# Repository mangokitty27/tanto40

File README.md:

# tanto40
A 40% keeb inspired by the Katana60

uses redragon low profile switches and arduino promicro

created in kicad

.dxf file show geometry of layout

qmk layout.hex made with https://kbfirmware.com/

redragon switch footprint from github.com/rgoulter

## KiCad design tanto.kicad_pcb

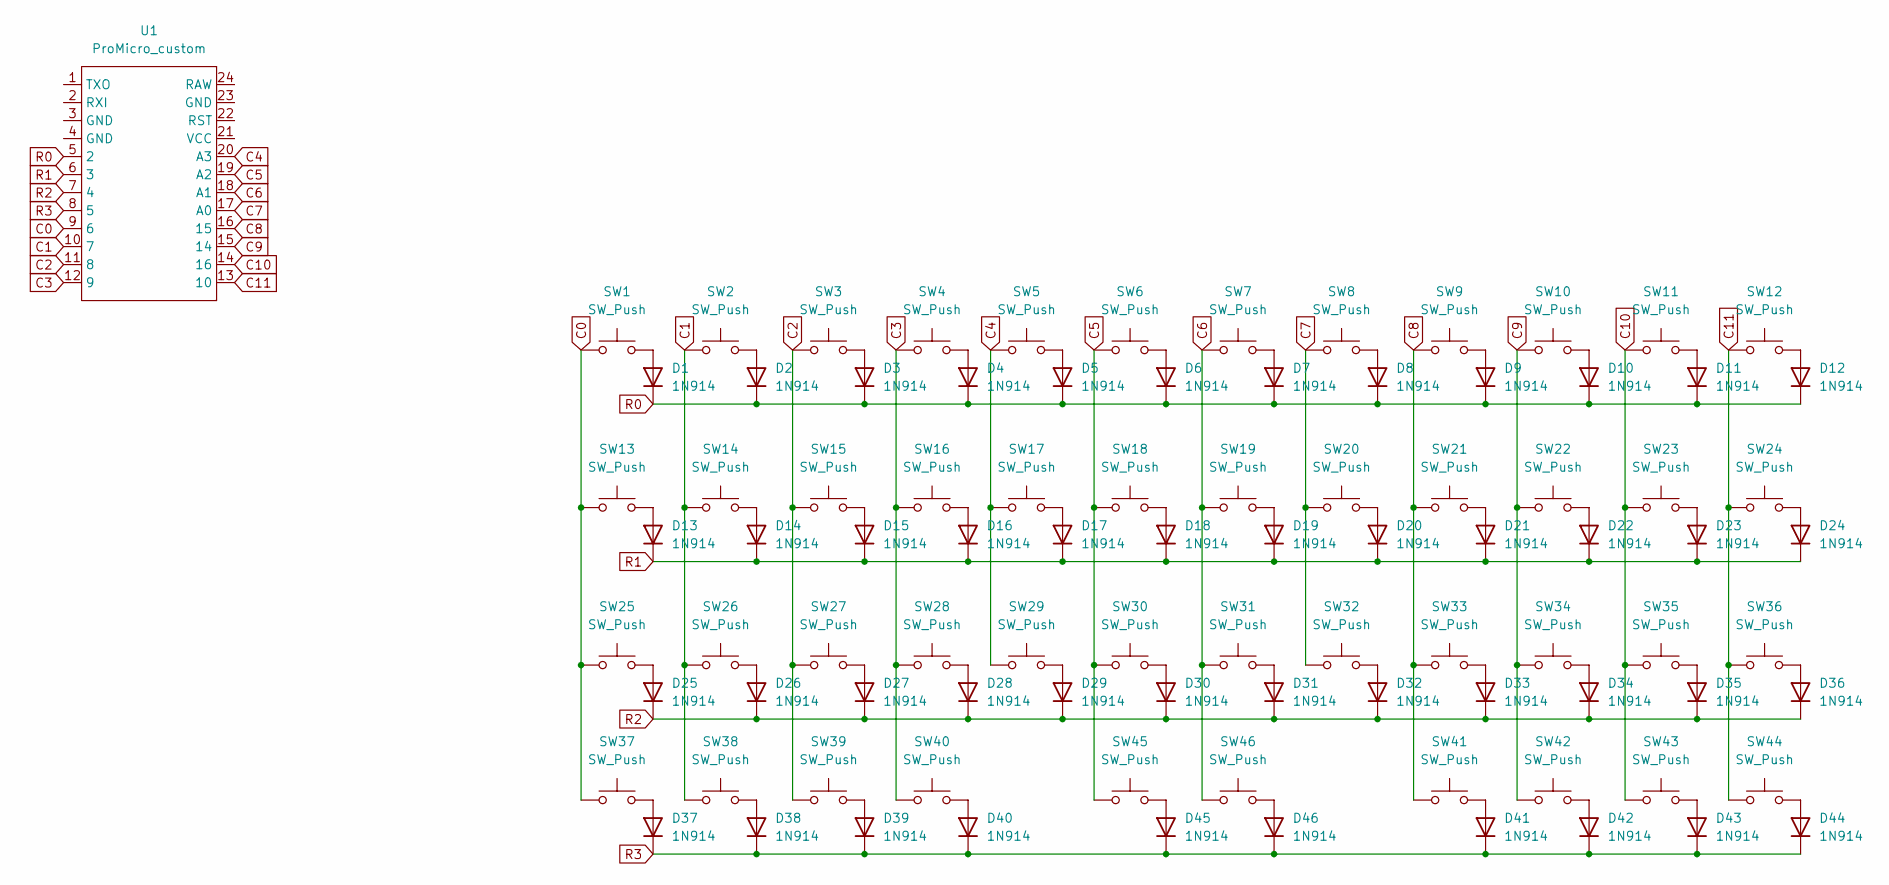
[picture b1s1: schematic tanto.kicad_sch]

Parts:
D1, D2, D3, D4, D5, D6, D7, D8, D9, D10, D11, D12, D13, D14, D15, D16, D17, D18, D19, D20, D21, D22, D23, D24, D25, D26, D27, D28, D29, D30, D31, D32, D33, D34, D35, D36, D37, D38, D39, D40, D41, D42, D43, D44, D45, D46: 1N914; D_DO-35_SOD27_P7.62mm_Horizontal
SW1, SW2, SW3, SW4, SW5, SW6, SW7, SW8, SW9, SW10, SW11, SW12, SW13, SW14, SW15, SW16, SW17, SW18, SW19, SW20, SW21, SW22, SW23, SW24, SW25, SW26, SW27, SW28, SW29, SW30, SW31, SW32, SW33, SW34, SW35, SW36, SW37, SW38, SW39, SW40, SW41, SW42, SW43, SW44, SW45, SW46: SW_Push; SW_Redragon_LowProfile_PCB_1.00u
U1: ProMicro_custom; ProMicro

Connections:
C0: SW1.1, SW13.1, SW25.1, SW37.1, U1.9 (6)
C1: SW2.1, SW14.1, SW26.1, SW38.1, U1.10 (7)
C2: SW3.1, SW15.1, SW27.1, SW39.1, U1.11 (8)
C3: SW4.1, SW16.1, SW28.1, SW40.1, U1.12 (9)
C4: SW5.1, SW17.1, SW29.1, U1.20 (A3)
C5: SW6.1, SW18.1, SW30.1, SW45.1, U1.19 (A2)
C6: SW7.1, SW19.1, SW31.1, SW46.1, U1.18 (A1)
C7: SW8.1, SW20.1, SW32.1, U1.17 (A0)
C8: SW9.1, SW21.1, SW33.1, SW41.1, U1.16 (15)
C9: SW10.1, SW22.1, SW34.1, SW42.1, U1.15 (14)
C10: SW11.1, SW23.1, SW35.1, SW43.1, U1.14 (16)
C11: SW12.1, SW24.1, SW36.1, SW44.1, U1.13 (10)
unnamed: D1.2 (A), SW1.2
unnamed: D2.2 (A), SW2.2
unnamed: D3.2 (A), SW3.2
unnamed: D4.2 (A), SW4.2
unnamed: D5.2 (A), SW5.2
unnamed: D6.2 (A), SW6.2
unnamed: D7.2 (A), SW7.2
unnamed: D8.2 (A), SW8.2
unnamed: D9.2 (A), SW9.2
unnamed: D10.2 (A), SW10.2
unnamed: D11.2 (A), SW11.2
unnamed: D12.2 (A), SW12.2
unnamed: D13.2 (A), SW13.2
unnamed: D14.2 (A), SW14.2
unnamed: D15.2 (A), SW15.2
unnamed: D16.2 (A), SW16.2
unnamed: D17.2 (A), SW17.2
unnamed: D18.2 (A), SW18.2
unnamed: D19.2 (A), SW19.2
unnamed: D20.2 (A), SW20.2
unnamed: D21.2 (A), SW21.2
unnamed: D22.2 (A), SW22.2
unnamed: D23.2 (A), SW23.2
unnamed: D24.2 (A), SW24.2
unnamed: D25.2 (A), SW25.2
unnamed: D26.2 (A), SW26.2
unnamed: D27.2 (A), SW27.2
unnamed: D28.2 (A), SW28.2
unnamed: D29.2 (A), SW29.2
unnamed: D30.2 (A), SW30.2
unnamed: D31.2 (A), SW31.2
unnamed: D32.2 (A), SW32.2
unnamed: D33.2 (A), SW33.2
unnamed: D34.2 (A), SW34.2
unnamed: D35.2 (A), SW35.2
unnamed: D36.2 (A), SW36.2
unnamed: D37.2 (A), SW37.2
unnamed: D38.2 (A), SW38.2
unnamed: D39.2 (A), SW39.2
unnamed: D40.2 (A), SW40.2
unnamed: D41.2 (A), SW41.2
unnamed: D42.2 (A), SW42.2
unnamed: D43.2 (A), SW43.2
unnamed: D44.2 (A), SW44.2
unnamed: D45.2 (A), SW45.2
unnamed: D46.2 (A), SW46.2
R0: D1.1 (K), D2.1 (K), D3.1 (K), D4.1 (K), D5.1 (K), D6.1 (K), D7.1 (K), D8.1 (K), D9.1 (K), D10.1 (K), D11.1 (K), D12.1 (K), U1.5 (2)
R1: D13.1 (K), D14.1 (K), D15.1 (K), D16.1 (K), D17.1 (K), D18.1 (K), D19.1 (K), D20.1 (K), D21.1 (K), D22.1 (K), D23.1 (K), D24.1 (K), U1.6 (3)
R2: D25.1 (K), D26.1 (K), D27.1 (K), D28.1 (K), D29.1 (K), D30.1 (K), D31.1 (K), D32.1 (K), D33.1 (K), D34.1 (K), D35.1 (K), D36.1 (K), U1.7 (4)
R3: D37.1 (K), D38.1 (K), D39.1 (K), D40.1 (K), D41.1 (K), D42.1 (K), D43.1 (K), D44.1 (K), D45.1 (K), D46.1 (K), U1.8 (5)

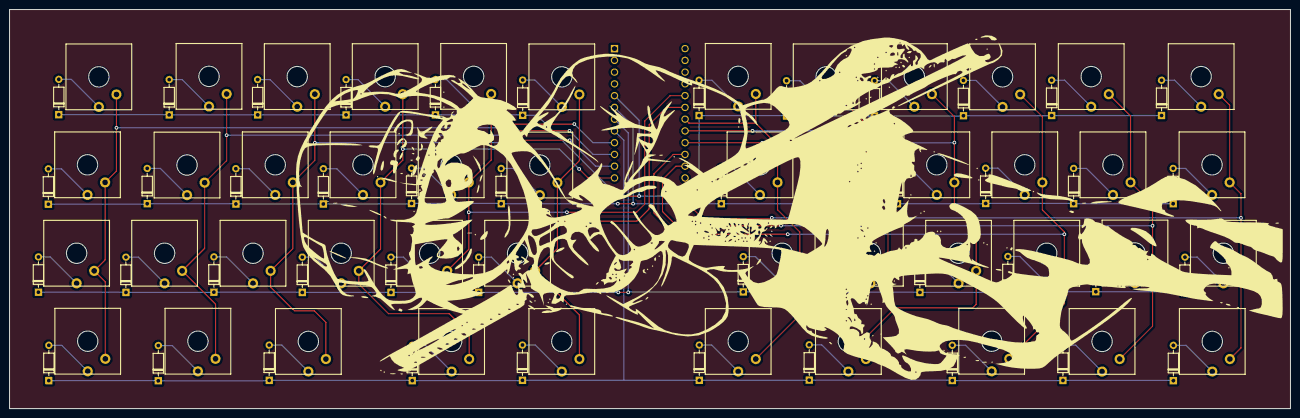
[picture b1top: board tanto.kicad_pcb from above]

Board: 2 copper layers, 276.7 x 86.2 mm, 93 parts (0 on the bottom side), 62 nets.
